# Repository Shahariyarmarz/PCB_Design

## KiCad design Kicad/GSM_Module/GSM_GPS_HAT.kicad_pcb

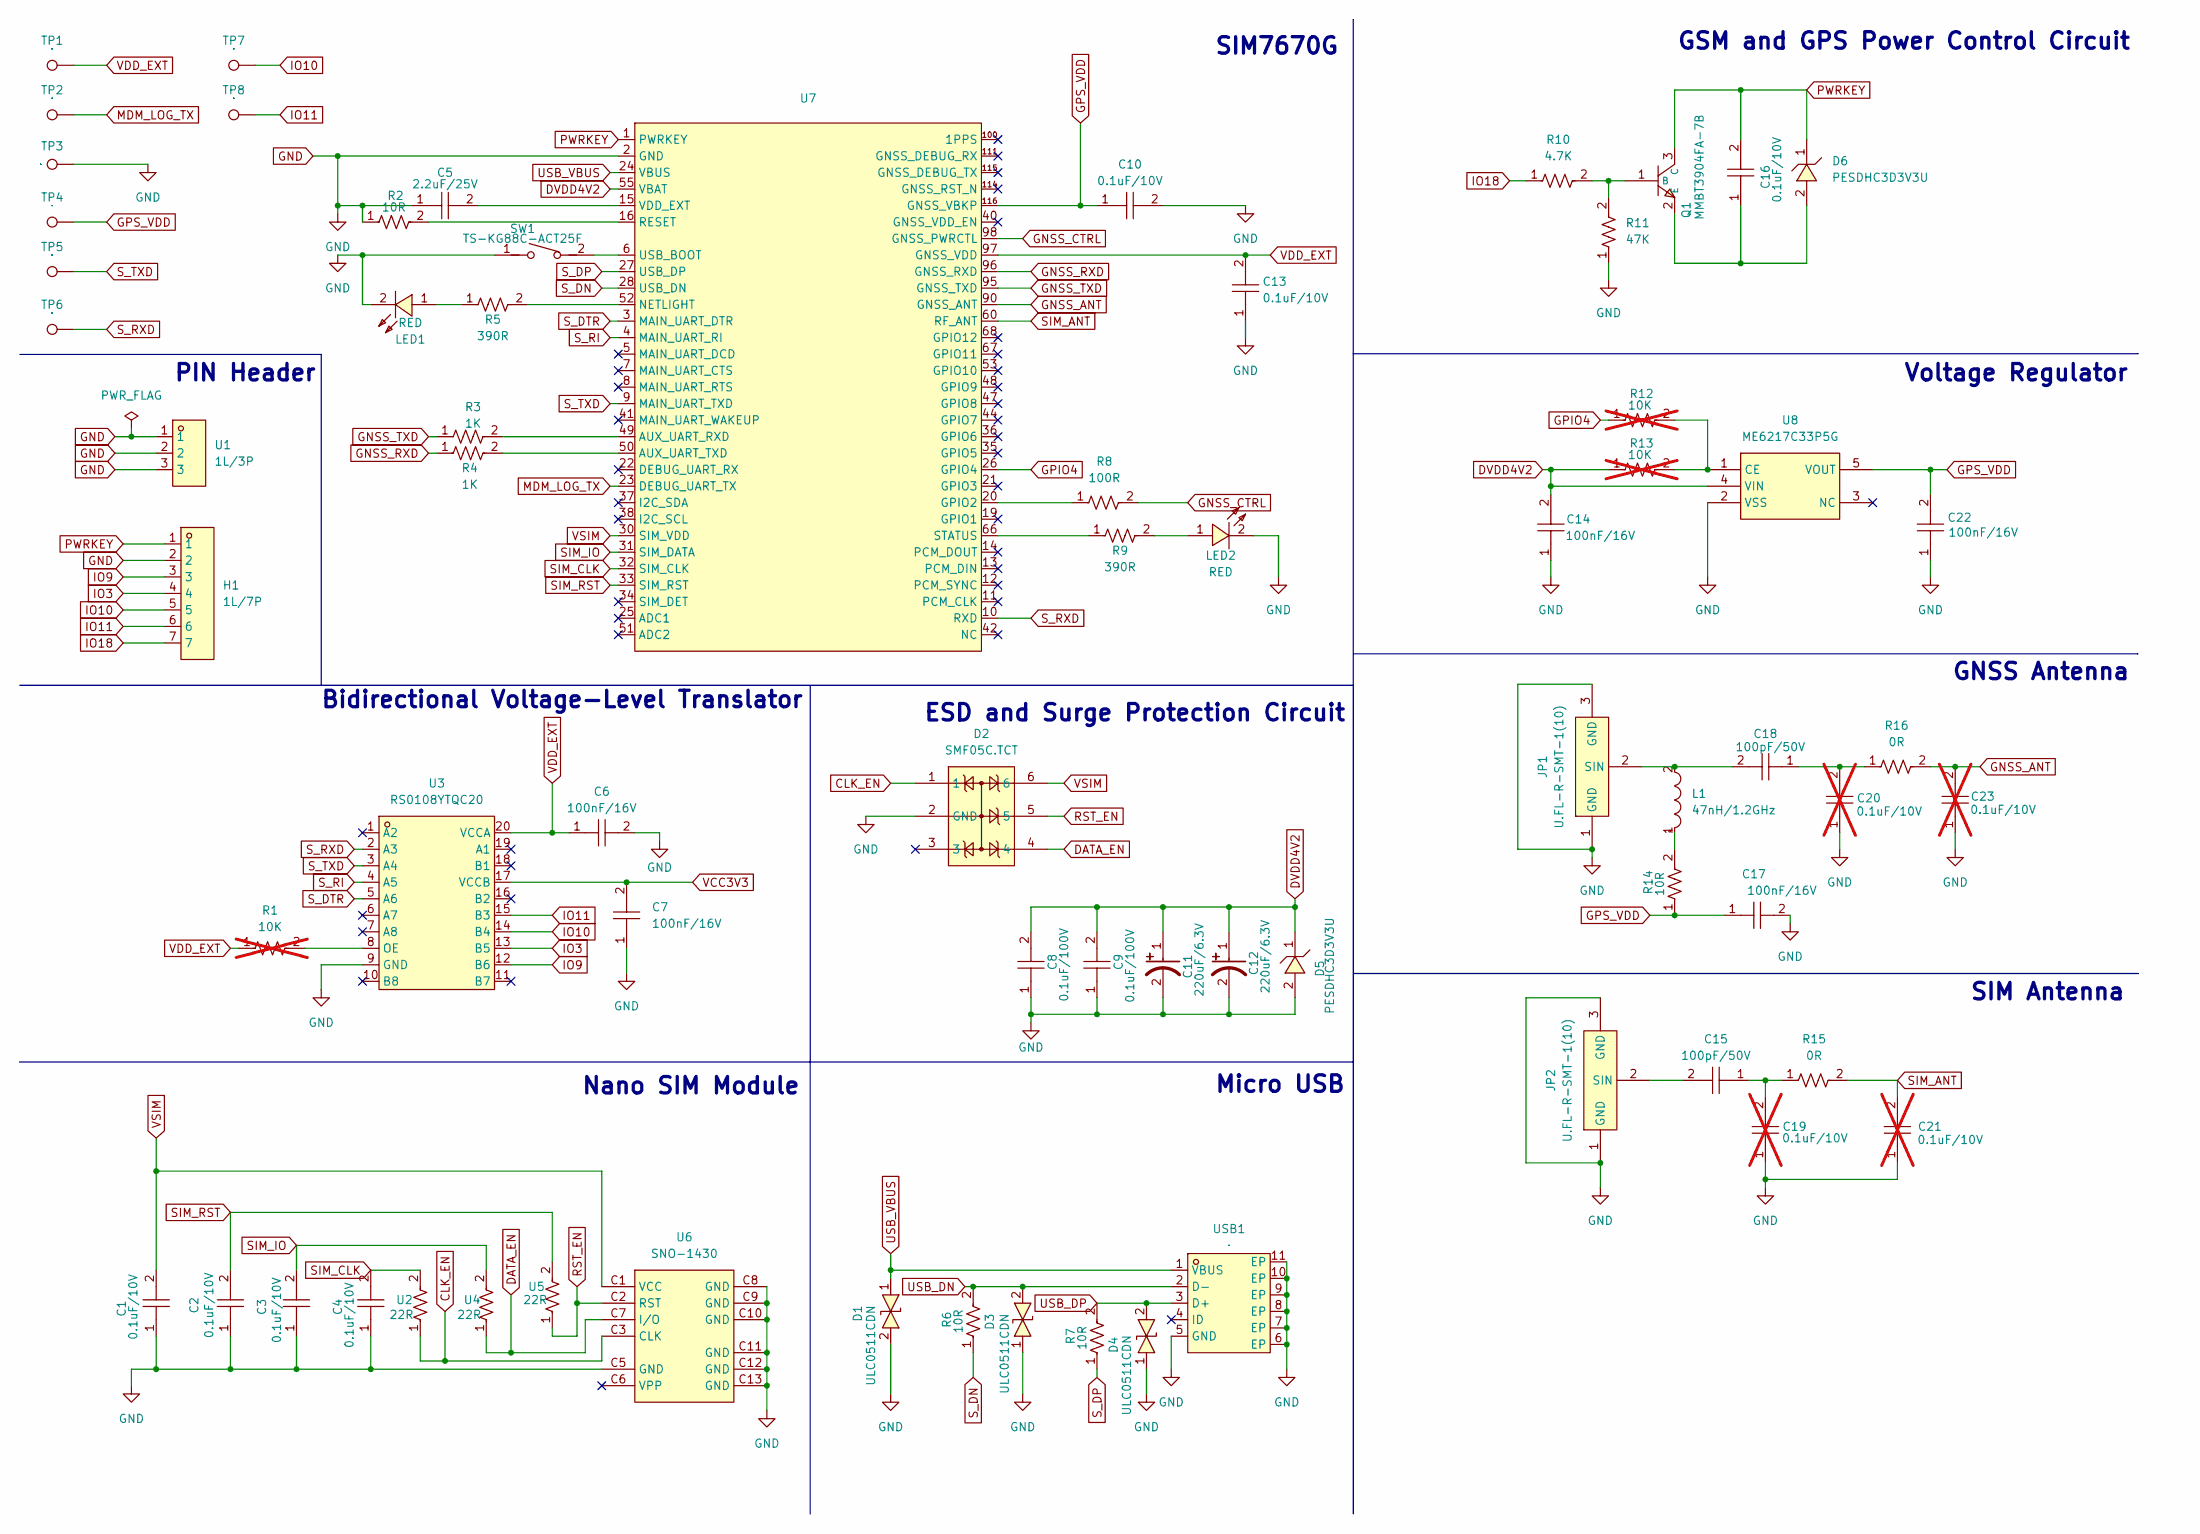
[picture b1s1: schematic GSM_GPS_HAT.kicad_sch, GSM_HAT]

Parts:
C1, C2, C3, C4, C10, C13, C16: 0.1uF/10V; C0402; LCSC Part C6955083
C5: 2.2uF/25V; C0402; LCSC Part C723363
C6, C7, C14, C17, C22: 100nF/16V; C0402; LCSC Part C541464
C8, C9: 0.1uF/100V; C0603; LCSC Part C3011705
C11, C12: 220uF/6.3V; CASE-B_3528; LCSC Part C30242
C15, C18: 100pF/50V; C0402; LCSC Part C327198
C19, C20, C21, C23: 0.1uF/10V; C0402; LCSC Part C6955083; not fitted
D1, D3, D4: ULC0511CDN; X1-DFN1006-2_L1.0-W0.6-RD; LCSC Part C384841
D2: SMF05C.TCT; SC-70-6_L2.2-W1.3-P0.65-LS2.1-BR; LCSC Part C85191
D5, D6: PESDHC3D3V3U; SOD-323_L1.8-W1.3-LS2.5-RD; LCSC Part C496538
H1: 1L/7P; HDR-TH_7P-P2.54-V-M; LCSC Part C706879
JP1, JP2: U.FL-R-SMT-1(10); ANT-SMD_UFL-R-SMT-1-10; LCSC Part C88373
L1: 47nH/1.2GHz; IND-SMD_L1.6-W0.8-RD; LCSC Part C162553
LED1, LED2: RED; LED0603-R-RD_RED; LCSC Part C83242
Q1: MMBT3904FA-7B; DFN-3L_L0.8-W0.6-P0.35-BR; LCSC Part C151577
R1, R12, R13: 10K; R0402; LCSC Part C513708; not fitted
R2, R6, R7, R14: 10R; R0402; LCSC Part C5455560
R3, R4: 1K; R0402; LCSC Part C445596
R5, R9: 390R; R0402; LCSC Part C227027
R8: 100R; R0402; LCSC Part C471762
R10: 4.7K; R0402; LCSC Part C105871
R11: 47K; R0402; LCSC Part C5447295
R15, R16: 0R; R0402; LCSC Part C106231
SW1: TS-KG88C-ACT25F; KEY-SMD_L4.0-W2.9-LS4.8; LCSC Part C2874431
TP1, TP2, TP3, TP4, TP5, TP6, TP7, TP8: TestPoint; TestPoint_Pad_D1.0mm
U1: 1L/3P; HDR-TH_3P-P2.54-V-M; LCSC Part C5445396
U2, U4, U5: 22R; R0402; LCSC Part C852651
U3: RS0108YTQC20; QFN-20_L3.0-W3.0-P0.40-BL-EP1.7; LCSC Part C5129983
U6: SNO-1430; SIM-SMD_HANBO_SNO-1430; LCSC Part C5310440
U7: LGA-124_L24.0-W24.0-P1.0-A7670C-LASS; Manufacturer Part SIM7670G; LCSC Part Name SIM7670G
U8: ME6217C33P5G; SOT-89-5_L4.5-W2.5-P1.50-LS4.5-BR; LCSC Part C81592
USB1: 1050171001; MICRO-USB-SMD_1050171001; LCSC Part C505111

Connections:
CLK_EN: D2.1, U2.1, U6.C3 (CLK)
DATA_EN: D2.4, U4.1, U6.C7 (I/O)
DVDD4V2: C8.2, C9.2, C11.1, C12.1, C14.2, D5.1 (C), R13.1, U7.55 (VBAT), U7.56 (VBAT), U7.57 (VBAT), U8.4 (VIN)
GND: C1.1, C2.1, C3.1, C4.1, C5.1, C6.2, C7.1, C8.1, C9.1, C10.2, C11.2, C12.2, C13.1, C14.1, C17.2, C19.1, C20.1, C21.1, C22.1, C23.1, D1.2, D2.2 (GND), D3.1, D4.1, D5.2 (A), H1.2, JP1.1 (GND), JP1.3 (GND), JP2.1 (GND), JP2.3 (GND), LED1.2 (C), LED2.2 (C), R2.1, R11.1, SW1.1, TP3.1, U1.1, U1.2, U1.3, U3.9 (GND), U3.21 (GND), U6.C5 (GND), U6.C8 (GND), U6.C9 (GND), U6.C10 (GND), U6.C11 (GND), U6.C12 (GND), U6.C13 (GND), U7.2 (GND), U7.17 (GND), U7.18 (GND), U7.29 (GND), U7.39 (GND), U7.45 (GND), U7.46 (GND), U7.54 (GND), U7.58 (GND), U7.59 (GND), U7.61 (GND), U7.62 (GND), U7.63 (GND), U7.64 (GND), U7.65 (GND), U7.69 (GND), U7.70 (GND), U7.71 (GND), U7.72 (GND), U7.73 (GND), U7.74 (GND), U7.75 (GND), U7.76 (GND), U7.77 (GND), U7.78 (GND), U7.79 (GND), U7.80 (GND), U7.81 (GND), U7.82 (GND), U7.83 (GND), U7.84 (GND), U7.85 (GND), U7.86 (GND), U7.87 (GND), U7.88 (GND), U7.89 (GND), U7.91 (GND), U7.92 (GND), U7.94 (GND), U8.2 (VSS), USB1.5 (GND), USB1.6 (EP), USB1.7 (EP), USB1.8 (EP), USB1.9 (EP), USB1.10 (EP), USB1.11 (EP)
GNSS_ANT: C23.2, R16.2, U7.90 (GNSS_ANT)
GNSS_CTRL: R8.2, U7.98 (GNSS_PWRCTL)
GNSS_RXD: R4.1, U7.96 (GNSS_RXD)
GNSS_TXD: R3.1, U7.95 (GNSS_TXD)
GPIO4: R12.1, U7.26 (GPIO4)
GPS_VDD: C10.1, C17.1, C22.2, R14.1, TP4.1, U7.116 (GNSS_VBKP), U8.5 (VOUT)
IO3: H1.4, U3.13 (B5)
IO9: H1.3, U3.12 (B6)
IO10: H1.5, TP7.1, U3.14 (B4)
IO11: H1.6, TP8.1, U3.15 (B3)
IO18: H1.7, R10.1
MDM_LOG_TX: TP2.1, U7.23 (DEBUG_UART_TX)
unnamed: C15.1, C19.2, R15.1
unnamed: C18.1, C20.2, R16.1
unnamed: C16.1, D6.2 (A), Q1.2 (E)
unnamed: C18.2, JP1.2 (SIN), L1.2
unnamed: C15.2, JP2.2 (SIN)
unnamed: L1.1, R14.2
unnamed: LED1.1 (A), R5.1
unnamed: LED2.1 (A), R9.2
unnamed: Q1.1 (B), R10.2, R11.2
unnamed: R1.2, U3.8 (OE)
unnamed: R3.2, U7.49 (AUX_UART_RXD)
unnamed: R4.2, U7.50 (AUX_UART_TXD)
unnamed: R8.1, U7.20 (GPIO2)
unnamed: R5.2, U7.52 (NETLIGHT)
unnamed: R2.2, U7.16 (RESET)
unnamed: R9.1, U7.66 (STATUS)
unnamed: SW1.2, U7.6 (USB_BOOT)
unnamed: C5.2, U7.15 (VDD_EXT)
unnamed: R12.2, R13.2, U8.1 (CE)
PWRKEY: C16.2, D6.1 (C), H1.1, Q1.3 (C), U7.1 (PWRKEY)
RST_EN: D2.5, U5.1, U6.C2 (RST)
SIM_ANT: C21.2, R15.2, U7.60 (RF_ANT)
SIM_CLK: C4.2, U2.2, U7.32 (SIM_CLK)
SIM_IO: C3.2, U4.2, U7.31 (SIM_DATA)
SIM_RST: C2.2, U5.2, U7.33 (SIM_RST)
S_DN: R6.1, U7.28 (USB_DN)
S_DP: R7.1, U7.27 (USB_DP)
S_DTR: U3.5 (A6), U7.3 (MAIN_UART_DTR)
S_RI: U3.4 (A5), U7.4 (MAIN_UART_RI)
S_RXD: TP6.1, U3.2 (A3), U7.10 (RXD)
S_TXD: TP5.1, U3.3 (A4), U7.9 (MAIN_UART_TXD)
USB_DN: D3.2, R6.2, USB1.2 (D-)
USB_DP: D4.2, R7.2, USB1.3 (D+)
USB_VBUS: D1.1, U7.24 (VBUS), USB1.1 (VBUS)
VCC3V3: C7.2, U3.17 (VCCB)
VSIM: C1.2, D2.6, U6.C1 (VCC), U7.30 (SIM_VDD)

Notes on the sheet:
Nano SIM Module
SIM7670G
Micro USB
GSM and GPS Power Control Circuit
PIN Header
Voltage Regulator
Bidirectional Voltage-Level Translator
SIM Antenna
GNSS Antenna
ESD and Surge Protection Circuit

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
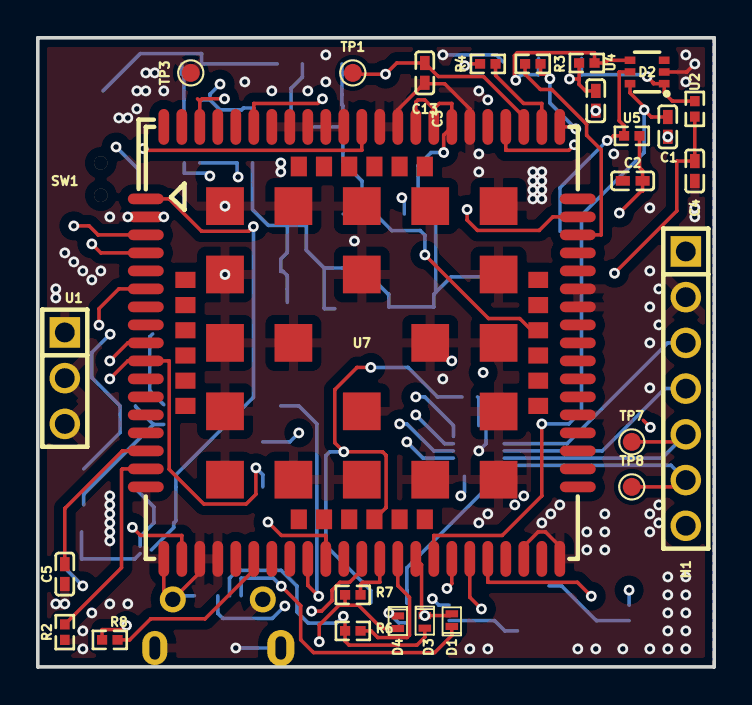
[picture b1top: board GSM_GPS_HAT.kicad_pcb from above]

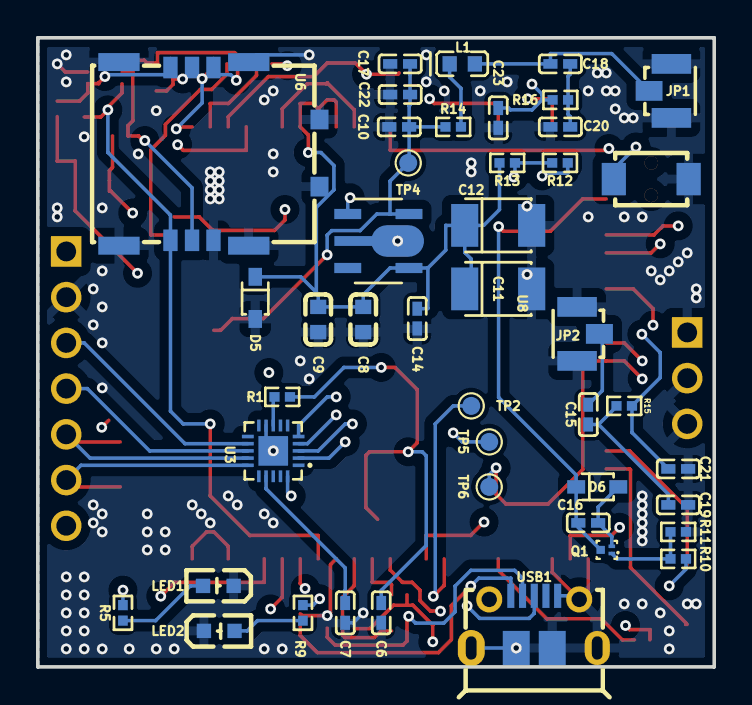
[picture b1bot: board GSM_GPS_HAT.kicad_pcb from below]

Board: 4 copper layers, 37.6 x 34.9 mm, 70 parts (44 on the bottom side), 53 nets.

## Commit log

2025-02-19 Kicad
2025-02-19 Rename README.txt to README.md
